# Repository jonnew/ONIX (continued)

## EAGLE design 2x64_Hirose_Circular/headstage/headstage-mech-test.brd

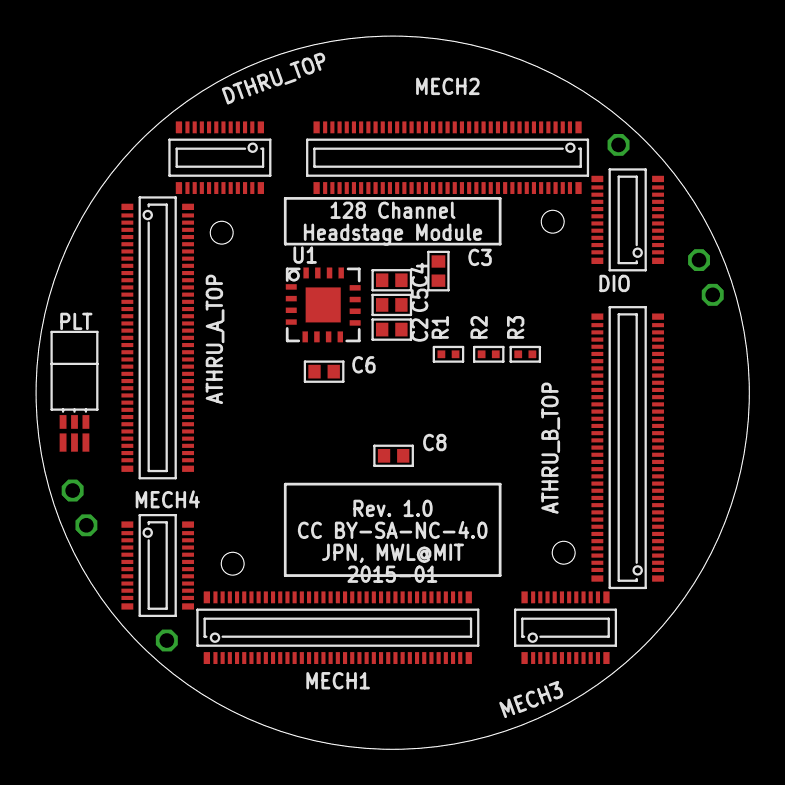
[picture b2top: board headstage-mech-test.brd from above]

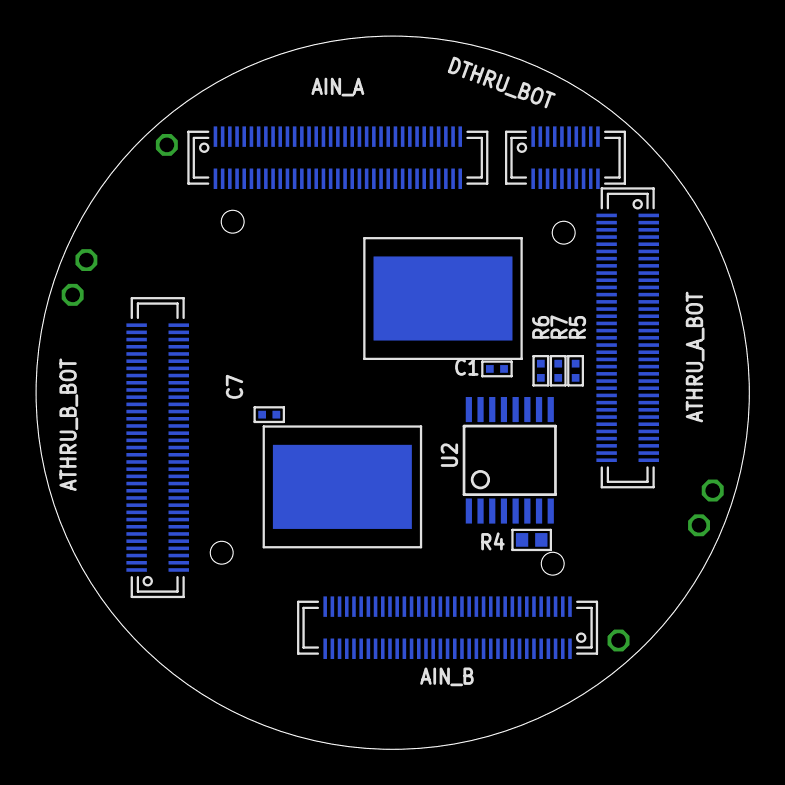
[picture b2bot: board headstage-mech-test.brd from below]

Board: 2 copper layers, 39.6 x 39.6 mm, 39 parts (14 on the bottom side), 168 nets, no tracks yet.

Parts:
AIN_A: DF40REC; DF40-70REC
AIN_B: DF40REC; DF40-70REC
ATHRU_A_BOT: DF40REC; DF40-70REC
ATHRU_A_TOP: DF40HEAD; DF40-70HEAD
ATHRU_B_BOT: DF40REC; DF40-70REC
ATHRU_B_TOP: DF40HEAD; DF40-70HEAD
C1, C7: 10n; 0201
C2, C3, C4, C5, C6, C8: .1uF; 0402
DIO: DF40HEAD; DF40-20HEAD
DTHRU_BOT: DF40REC; DF40-20REC
DTHRU_TOP: DF40HEAD; DF40-20HEAD
E$1, E$2: RHD2164_COB_MECH
GND, GND.: GND; TESTPOINT_SMALL
MECH1, MECH2: DF40HEAD; DF40-70HEAD
MECH3, MECH4: DF40HEAD; DF40-20HEAD
PLT: PZN-06; OMNETICS_PZN-06-AA
R1, R2, R3: 100; 0201
R4: 0; 0402
R5, R6, R7: 100k; 0201
REF1, REF2: REF; TESTPOINT_SMALL
U1: ADXL335
U2: 74HC4053; TSSOP-16
VCC1, VCC2: VCC; TESTPOINT_SMALL

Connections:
AGND_THRU_1: ATHRU_A_BOT.34, ATHRU_A_BOT.35, ATHRU_A_TOP.34, ATHRU_A_TOP.35
AGND_THRU_2: ATHRU_A_BOT.69, ATHRU_A_BOT.70, ATHRU_A_TOP.69, ATHRU_A_TOP.70
AGND_THRU_3: ATHRU_B_BOT.34, ATHRU_B_BOT.35, ATHRU_B_TOP.34, ATHRU_B_TOP.35
AGND_THRU_4: ATHRU_B_BOT.69, ATHRU_B_BOT.70, ATHRU_B_TOP.69, ATHRU_B_TOP.70
AUXOUT_A_THRU: DTHRU_BOT.4, DTHRU_TOP.4
AUXOUT_B_THRU: DTHRU_BOT.5, DTHRU_TOP.5
BATH: PLT.B1, U2.3
CS+: DIO.12, R1.2
CS+_THRU: DTHRU_BOT.12, DTHRU_TOP.12
CS-: DIO.11, R1.1
CS-_THRU: DTHRU_BOT.11, DTHRU_TOP.11
DGND_THRU: DTHRU_BOT.1, DTHRU_BOT.2, DTHRU_BOT.3, DTHRU_BOT.6, DTHRU_BOT.7, DTHRU_BOT.8, DTHRU_BOT.9, DTHRU_TOP.1, DTHRU_TOP.2, DTHRU_TOP.3, DTHRU_TOP.6, DTHRU_TOP.7, DTHRU_TOP.8, DTHRU_TOP.9
GND: AIN_A.34, AIN_A.35, AIN_A.69, AIN_A.70, AIN_B.34, AIN_B.35, AIN_B.69, AIN_B.70, C1.2, C2.2, C3.2, C4.1, C5.1, C6.1, C7.2, C8.2, DIO.1, DIO.2, DIO.3, DIO.5, DIO.6, DIO.7, GND.1, GND..1, PLT.B3, R4.1, R5.1, R6.1, R7.1, U1.COM1, U1.COM2, U1.COM3, U1.COM4, U1.ST, U2.6, U2.7, U2.8
MISO1+_THRU: DTHRU_BOT.18, DTHRU_TOP.18
MISO1-_THRU: DTHRU_BOT.17, DTHRU_TOP.17
MISO2+_THRU: DTHRU_BOT.20, DTHRU_TOP.20
MISO2-_THRU: DTHRU_BOT.19, DTHRU_TOP.19
MOSI+: DIO.16, R3.2
MOSI+_THRU: DTHRU_BOT.16, DTHRU_TOP.16
MOSI-: DIO.15, R3.1
MOSI-_THRU: DTHRU_BOT.15, DTHRU_TOP.15
unnamed: ATHRU_B_BOT.33, ATHRU_B_TOP.33
unnamed: ATHRU_B_BOT.32, ATHRU_B_TOP.32
unnamed: ATHRU_B_BOT.31, ATHRU_B_TOP.31
unnamed: ATHRU_B_BOT.30, ATHRU_B_TOP.30
unnamed: ATHRU_B_BOT.29, ATHRU_B_TOP.29
unnamed: ATHRU_B_BOT.28, ATHRU_B_TOP.28
unnamed: ATHRU_B_BOT.27, ATHRU_B_TOP.27
unnamed: ATHRU_B_BOT.26, ATHRU_B_TOP.26
unnamed: ATHRU_B_BOT.25, ATHRU_B_TOP.25
unnamed: ATHRU_B_BOT.24, ATHRU_B_TOP.24
unnamed: ATHRU_B_BOT.23, ATHRU_B_TOP.23
unnamed: ATHRU_B_BOT.22, ATHRU_B_TOP.22
unnamed: ATHRU_B_BOT.21, ATHRU_B_TOP.21
unnamed: ATHRU_B_BOT.20, ATHRU_B_TOP.20
unnamed: ATHRU_B_BOT.19, ATHRU_B_TOP.19
unnamed: ATHRU_B_BOT.18, ATHRU_B_TOP.18
unnamed: ATHRU_B_BOT.17, ATHRU_B_TOP.17
unnamed: ATHRU_B_BOT.16, ATHRU_B_TOP.16
unnamed: ATHRU_B_BOT.15, ATHRU_B_TOP.15
unnamed: ATHRU_B_BOT.14, ATHRU_B_TOP.14
unnamed: ATHRU_B_BOT.13, ATHRU_B_TOP.13
unnamed: ATHRU_B_BOT.12, ATHRU_B_TOP.12
unnamed: ATHRU_B_BOT.11, ATHRU_B_TOP.11
unnamed: PLT.T1, R7.2, U2.11
unnamed: PLT.T2, R6.2, U2.10
unnamed: PLT.T3, R5.2, U2.9
unnamed: R4.2, U2.5
unnamed: PLT.B2, U2.1, U2.13
unnamed: ATHRU_B_BOT.10, ATHRU_B_TOP.10
unnamed: ATHRU_B_BOT.9, ATHRU_B_TOP.9
unnamed: ATHRU_B_BOT.8, ATHRU_B_TOP.8
unnamed: ATHRU_B_BOT.7, ATHRU_B_TOP.7
unnamed: ATHRU_B_BOT.6, ATHRU_B_TOP.6
unnamed: ATHRU_B_BOT.5, ATHRU_B_TOP.5
unnamed: ATHRU_B_BOT.4, ATHRU_B_TOP.4
unnamed: ATHRU_B_BOT.3, ATHRU_B_TOP.3
unnamed: ATHRU_B_BOT.2, ATHRU_B_TOP.2
unnamed: ATHRU_B_BOT.38, ATHRU_B_TOP.38
unnamed: ATHRU_B_BOT.39, ATHRU_B_TOP.39
unnamed: ATHRU_B_BOT.40, ATHRU_B_TOP.40
unnamed: ATHRU_B_BOT.41, ATHRU_B_TOP.41
unnamed: ATHRU_B_BOT.42, ATHRU_B_TOP.42
unnamed: ATHRU_B_BOT.43, ATHRU_B_TOP.43
unnamed: ATHRU_B_BOT.44, ATHRU_B_TOP.44
unnamed: ATHRU_B_BOT.45, ATHRU_B_TOP.45
unnamed: ATHRU_B_BOT.46, ATHRU_B_TOP.46
unnamed: ATHRU_B_BOT.47, ATHRU_B_TOP.47
unnamed: ATHRU_B_BOT.48, ATHRU_B_TOP.48
unnamed: ATHRU_B_BOT.49, ATHRU_B_TOP.49
unnamed: ATHRU_B_BOT.50, ATHRU_B_TOP.50
unnamed: ATHRU_B_BOT.51, ATHRU_B_TOP.51
unnamed: ATHRU_B_BOT.52, ATHRU_B_TOP.52
unnamed: ATHRU_B_BOT.53, ATHRU_B_TOP.53
unnamed: ATHRU_B_BOT.54, ATHRU_B_TOP.54
unnamed: ATHRU_B_BOT.55, ATHRU_B_TOP.55
unnamed: ATHRU_B_BOT.56, ATHRU_B_TOP.56
unnamed: ATHRU_B_BOT.57, ATHRU_B_TOP.57
unnamed: ATHRU_B_BOT.58, ATHRU_B_TOP.58
unnamed: ATHRU_B_BOT.59, ATHRU_B_TOP.59
unnamed: ATHRU_B_BOT.60, ATHRU_B_TOP.60
unnamed: ATHRU_B_BOT.61, ATHRU_B_TOP.61
unnamed: ATHRU_B_BOT.62, ATHRU_B_TOP.62
unnamed: ATHRU_B_BOT.63, ATHRU_B_TOP.63
unnamed: ATHRU_B_BOT.64, ATHRU_B_TOP.64
unnamed: ATHRU_B_BOT.65, ATHRU_B_TOP.65
unnamed: ATHRU_B_BOT.66, ATHRU_B_TOP.66
unnamed: ATHRU_B_BOT.67, ATHRU_B_TOP.67
unnamed: ATHRU_B_BOT.68, ATHRU_B_TOP.68
unnamed: ATHRU_A_BOT.33, ATHRU_A_TOP.33
unnamed: ATHRU_A_BOT.32, ATHRU_A_TOP.32
unnamed: ATHRU_A_BOT.31, ATHRU_A_TOP.31
unnamed: ATHRU_A_BOT.30, ATHRU_A_TOP.30
unnamed: ATHRU_A_BOT.29, ATHRU_A_TOP.29
unnamed: ATHRU_A_BOT.28, ATHRU_A_TOP.28
unnamed: ATHRU_A_BOT.27, ATHRU_A_TOP.27
unnamed: ATHRU_A_BOT.26, ATHRU_A_TOP.26
unnamed: ATHRU_A_BOT.25, ATHRU_A_TOP.25
unnamed: ATHRU_A_BOT.24, ATHRU_A_TOP.24
unnamed: ATHRU_A_BOT.23, ATHRU_A_TOP.23
unnamed: ATHRU_A_BOT.22, ATHRU_A_TOP.22
unnamed: ATHRU_A_BOT.21, ATHRU_A_TOP.21
unnamed: ATHRU_A_BOT.20, ATHRU_A_TOP.20
unnamed: ATHRU_A_BOT.19, ATHRU_A_TOP.19
unnamed: ATHRU_A_BOT.18, ATHRU_A_TOP.18
unnamed: ATHRU_A_BOT.17, ATHRU_A_TOP.17
unnamed: ATHRU_A_BOT.16, ATHRU_A_TOP.16
unnamed: ATHRU_A_BOT.15, ATHRU_A_TOP.15
unnamed: ATHRU_A_BOT.14, ATHRU_A_TOP.14
unnamed: ATHRU_A_BOT.13, ATHRU_A_TOP.13
unnamed: ATHRU_A_BOT.12, ATHRU_A_TOP.12
unnamed: ATHRU_A_BOT.11, ATHRU_A_TOP.11
unnamed: ATHRU_A_BOT.10, ATHRU_A_TOP.10
unnamed: ATHRU_A_BOT.9, ATHRU_A_TOP.9
unnamed: ATHRU_A_BOT.8, ATHRU_A_TOP.8
unnamed: ATHRU_A_BOT.7, ATHRU_A_TOP.7
unnamed: ATHRU_A_BOT.6, ATHRU_A_TOP.6
unnamed: ATHRU_A_BOT.5, ATHRU_A_TOP.5
unnamed: ATHRU_A_BOT.4, ATHRU_A_TOP.4
unnamed: ATHRU_A_BOT.3, ATHRU_A_TOP.3
unnamed: ATHRU_A_BOT.2, ATHRU_A_TOP.2
unnamed: ATHRU_A_BOT.38, ATHRU_A_TOP.38
unnamed: ATHRU_A_BOT.39, ATHRU_A_TOP.39
unnamed: ATHRU_A_BOT.40, ATHRU_A_TOP.40
unnamed: ATHRU_A_BOT.41, ATHRU_A_TOP.41
unnamed: ATHRU_A_BOT.42, ATHRU_A_TOP.42
unnamed: ATHRU_A_BOT.43, ATHRU_A_TOP.43
unnamed: ATHRU_A_BOT.44, ATHRU_A_TOP.44
unnamed: ATHRU_A_BOT.45, ATHRU_A_TOP.45
unnamed: ATHRU_A_BOT.46, ATHRU_A_TOP.46
unnamed: ATHRU_A_BOT.47, ATHRU_A_TOP.47
unnamed: ATHRU_A_BOT.48, ATHRU_A_TOP.48
unnamed: ATHRU_A_BOT.49, ATHRU_A_TOP.49
unnamed: ATHRU_A_BOT.50, ATHRU_A_TOP.50
unnamed: ATHRU_A_BOT.51, ATHRU_A_TOP.51
unnamed: ATHRU_A_BOT.52, ATHRU_A_TOP.52
unnamed: ATHRU_A_BOT.53, ATHRU_A_TOP.53
unnamed: ATHRU_A_BOT.54, ATHRU_A_TOP.54
unnamed: ATHRU_A_BOT.55, ATHRU_A_TOP.55
unnamed: ATHRU_A_BOT.56, ATHRU_A_TOP.56
unnamed: ATHRU_A_BOT.57, ATHRU_A_TOP.57
unnamed: ATHRU_A_BOT.58, ATHRU_A_TOP.58
unnamed: ATHRU_A_BOT.59, ATHRU_A_TOP.59
unnamed: ATHRU_A_BOT.60, ATHRU_A_TOP.60
unnamed: ATHRU_A_BOT.61, ATHRU_A_TOP.61
unnamed: ATHRU_A_BOT.62, ATHRU_A_TOP.62
unnamed: ATHRU_A_BOT.63, ATHRU_A_TOP.63
unnamed: ATHRU_A_BOT.64, ATHRU_A_TOP.64
unnamed: ATHRU_A_BOT.65, ATHRU_A_TOP.65
unnamed: ATHRU_A_BOT.66, ATHRU_A_TOP.66
unnamed: ATHRU_A_BOT.67, ATHRU_A_TOP.67
unnamed: ATHRU_A_BOT.68, ATHRU_A_TOP.68
unnamed: ATHRU_B_BOT.37, ATHRU_B_TOP.37
unnamed: ATHRU_A_BOT.37, ATHRU_A_TOP.37
REF: AIN_A.1, AIN_A.36, AIN_B.1, AIN_B.36, REF1.1, REF2.1, U2.4
REF_THRU_1: ATHRU_A_BOT.36, ATHRU_A_TOP.36
REF_THRU_2: ATHRU_A_BOT.1, ATHRU_A_TOP.1
REF_THRU_3: ATHRU_B_BOT.36, ATHRU_B_TOP.36
REF_THRU_4: ATHRU_B_BOT.1, ATHRU_B_TOP.1
SCLK+: DIO.14, R2.2
SCLK+_THRU: DTHRU_BOT.14, DTHRU_TOP.14
SCLK-: DIO.13, R2.1
SCLK-_THRU: DTHRU_BOT.13, DTHRU_TOP.13
VCC: C2.1, C3.1, C8.1, DIO.8, DIO.9, DIO.10, U1.VS1, U1.VS2, U2.16, VCC1.1, VCC2.1
VDD_THRU: DTHRU_BOT.10, DTHRU_TOP.10
XOUT1: C4.2, U1.XOUT
YOUT1: C5.2, U1.YOUT
ZOUT1: C6.2, U1.ZOUT

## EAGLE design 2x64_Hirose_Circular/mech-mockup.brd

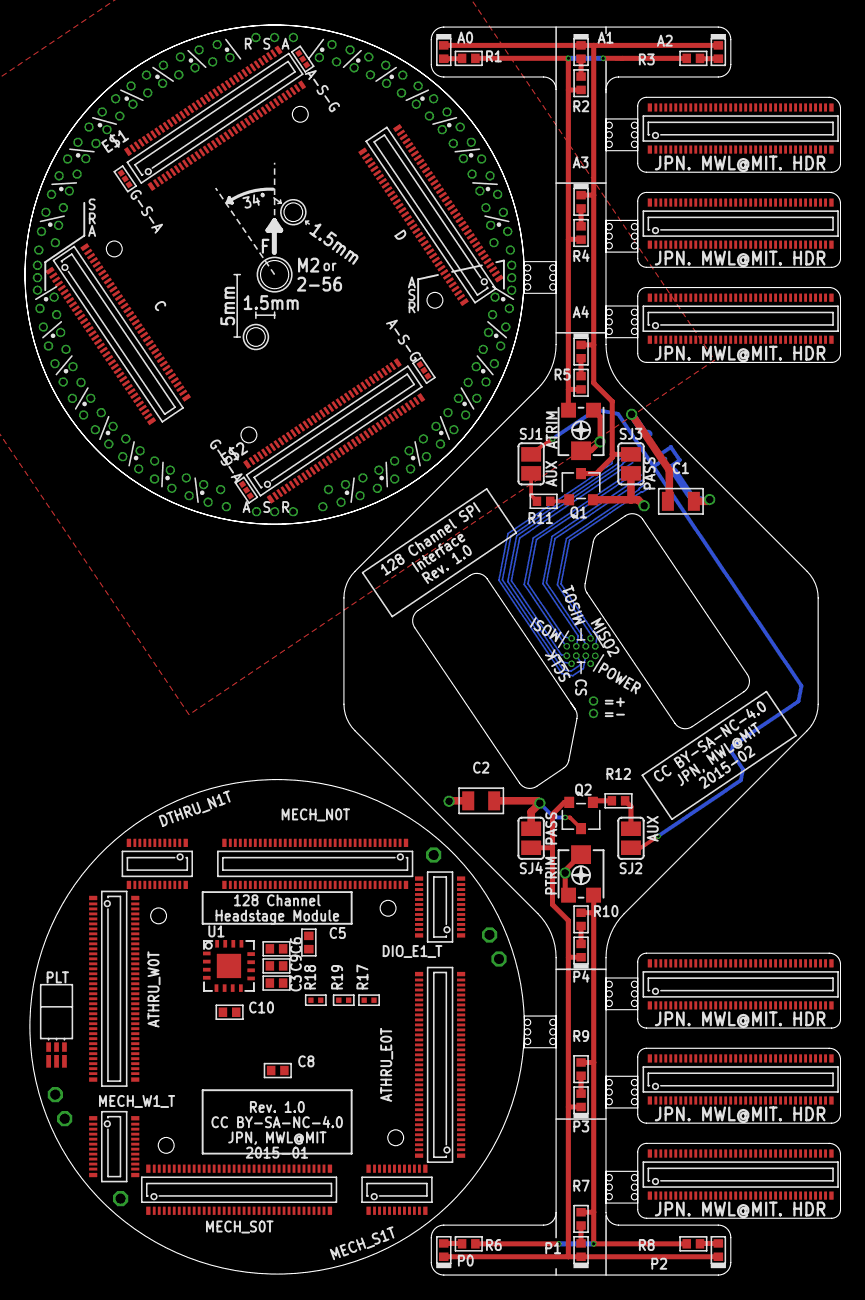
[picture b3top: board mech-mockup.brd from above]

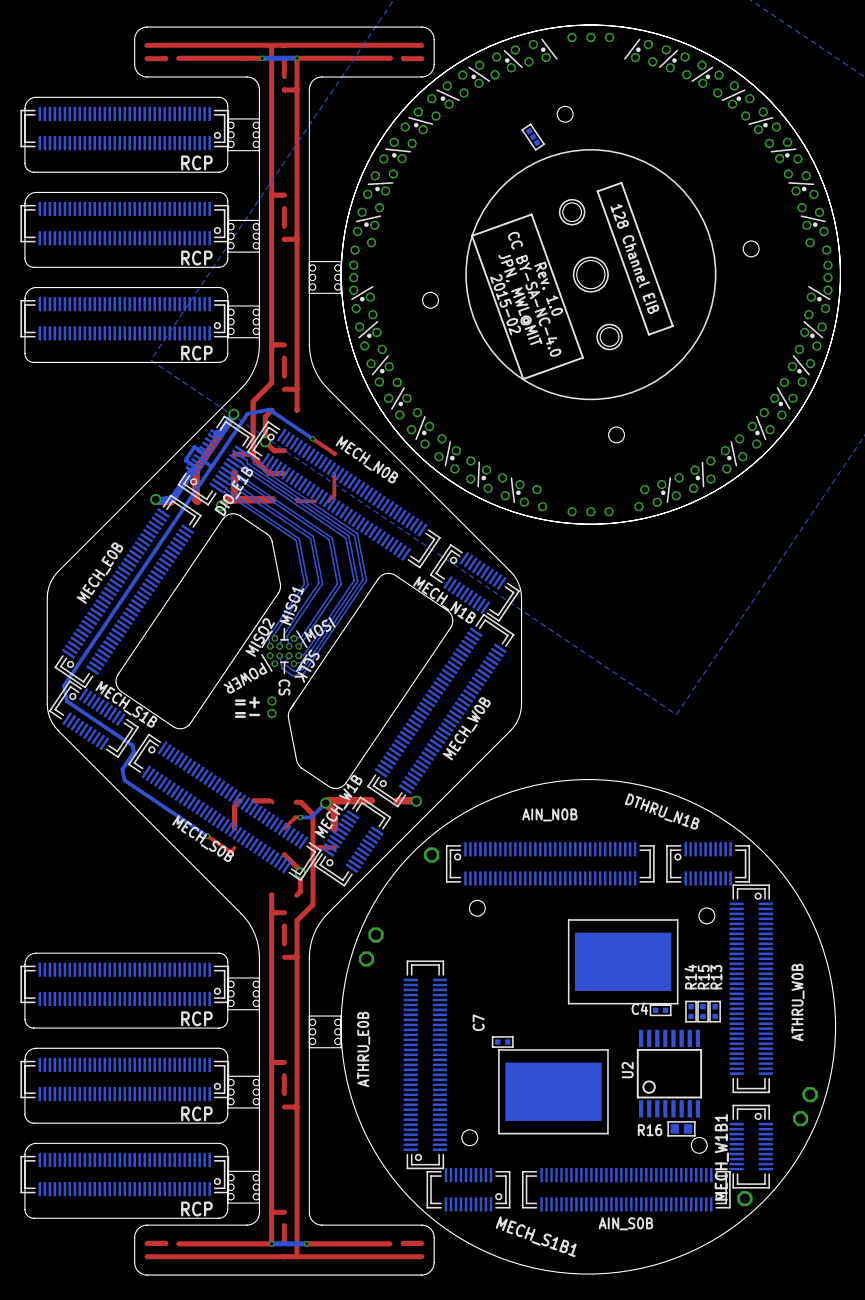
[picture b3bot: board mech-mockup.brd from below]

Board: 4 copper layers, 65.3 x 100.2 mm, 159 parts (48 on the bottom side), 32 nets.

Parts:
A0, A1, A2, A3, A4: RED; LED-0402
AGND_A0, AGND_A1: LRG_GP; GOLDPIN_0.5ID_0.7OD
AGND_B0, AGND_B1: LRG_GP; GOLDPIN_0.5ID_0.7OD
AIN_N0B: DF40REC; DF40-70REC
AIN_S0B: DF40REC; DF40-70REC
ATHRU_A_BOT, ATHRU_A_BOT1, ATHRU_A_BOT2, ATHRU_A_BOT3, ATHRU_A_BOT4, ATHRU_A_BOT5: DF40REC; DF40-70REC
ATHRU_A_TOP, ATHRU_A_TOP1, ATHRU_A_TOP2, ATHRU_A_TOP3, ATHRU_A_TOP4, ATHRU_A_TOP5: DF40HEAD; DF40-70HEAD
ATHRU_E0B: DF40REC; DF40-70REC
ATHRU_E0T: DF40HEAD; DF40-70HEAD
ATHRU_W0B: DF40REC; DF40-70REC
ATHRU_W0T: DF40HEAD; DF40-70HEAD
ATRIM: 2k; EIA/EIAJ
C: DF40HEAD; DF40-70HEAD
C1, C2: 10uF; 0805
C3, C5, C6, C8, C9, C10: .1uF; 0402
C4, C7: 10n; 0201
CS+: TP_SPI_WIRE+; SPI_WIRE+
CS-: TP_SPI_WIRE-; SPI_WIRE-
D: DF40HEAD; DF40-70HEAD
DIO_E1B: DF40-20REC
DIO_E1_T: DF40HEAD; DF40-20HEAD
DTHRU_N1B: DF40REC; DF40-20REC
DTHRU_N1T: DF40HEAD; DF40-20HEAD
E$1, E$2: DF40-70HEAD
E$3, E$4: RHD2164_COB_MECH
GND: TP_SPI_WIRE-; SPI_WIRE-
GND1, GND.: GND; TESTPOINT_SMALL
MECH_E0B: DF40-70REC
MECH_N0B: DF40-70REC
MECH_N0T: DF40HEAD; DF40-70HEAD
MECH_N1B: DF40-20REC
MECH_S0B: DF40-70REC
MECH_S0T: DF40HEAD; DF40-70HEAD
MECH_S1B: DF40-20REC
MECH_S1B1: DF40REC; DF40-20REC
MECH_S1T: DF40HEAD; DF40-20HEAD
MECH_W0B: DF40-70REC
MECH_W1B: DF40-20REC
MECH_W1B1: DF40REC; DF40-20REC
MECH_W1_T: DF40HEAD; DF40-20HEAD
MIS02+: TP_SPI_WIRE+; SPI_WIRE+
MISO1+: TP_SPI_WIRE+; SPI_WIRE+
MISO1-, MISO2-: TP_SPI_WIRE-; SPI_WIRE-
MOSI+: TP_SPI_WIRE+; SPI_WIRE+
MOSI-: TP_SPI_WIRE-; SPI_WIRE-
P0, P1, P2, P3, P4: BLUE; LED-0402
PLT: PZN-06; OMNETICS_PZN-06-AA
PTRIM: 2k; EIA/EIAJ
Q1: SSM3K324; SOT23-GSD
Q2: SSM3J328; SOT23-GSD
R1, R2, R3, R4, R5, R6, R7, R8, R9, R10: 82; 0402
R11, R12: 470; 0402
R13, R14, R15: 100k; 0201
R16: 0; 0402
R17, R18, R19: 100; 0201
REF1, REF2: REF; TESTPOINT_SMALL
REF_A0, REF_A1: LRG_GP; GOLDPIN_0.5ID_0.7OD
REF_B0, REF_B1: LRG_GP; GOLDPIN_0.5ID_0.7OD
SCLK+: TP_SPI_WIRE+; SPI_WIRE+
SCLK-: TP_SPI_WIRE-; SPI_WIRE-
SHLD_A0, SHLD_A1: LRG_GP; GOLDPIN_0.5ID_0.7OD
SHLD_B0, SHLD_B1: LRG_GP; GOLDPIN_0.5ID_0.7OD
SJ1, SJ2: AUX; SJ
SJ3, SJ4: PASS; SJ
SJ_A0, SJ_A1, SJ_A2: SJ_2_0201
SJ_B0, SJ_B1: SJ_2_0201
TET0: 0; TETRODE_128_0.5ID_0.7OD
TET1: 1; TETRODE_128_0.5ID_0.7OD
TET2: 2; TETRODE_128_0.5ID_0.7OD
TET3: 3; TETRODE_128_0.5ID_0.7OD
TET4: 4; TETRODE_128_0.5ID_0.7OD
TET5: 5; TETRODE_128_0.5ID_0.7OD
TET6: 6; TETRODE_128_0.5ID_0.7OD
TET7: 7; TETRODE_128_0.5ID_0.7OD
TET8: 8; TETRODE_128_0.5ID_0.7OD
TET9: 9; TETRODE_128_0.5ID_0.7OD
TET10: 10; TETRODE_128_0.5ID_0.7OD
TET11: 11; TETRODE_128_0.5ID_0.7OD
TET12: 12; TETRODE_128_0.5ID_0.7OD
TET13: 13; TETRODE_128_0.5ID_0.7OD
TET14: 14; TETRODE_128_0.5ID_0.7OD
TET15: 15; TETRODE_128_0.5ID_0.7OD
TET16: 16; TETRODE_128_0.5ID_0.7OD
TET17: 17; TETRODE_128_0.5ID_0.7OD
TET18: 18; TETRODE_128_0.5ID_0.7OD
TET19: 19; TETRODE_128_0.5ID_0.7OD
TET20: 20; TETRODE_128_0.5ID_0.7OD
TET21: 21; TETRODE_128_0.5ID_0.7OD
TET22: 22; TETRODE_128_0.5ID_0.7OD
TET23: 23; TETRODE_128_0.5ID_0.7OD
TET24: 24; TETRODE_128_0.5ID_0.7OD
TET25: 25; TETRODE_128_0.5ID_0.7OD
TET26: 26; TETRODE_128_0.5ID_0.7OD
TET27: 27; TETRODE_128_0.5ID_0.7OD
TET28: 28; TETRODE_128_0.5ID_0.7OD
TET29: 29; TETRODE_128_0.5ID_0.7OD
TET30: 30; TETRODE_128_0.5ID_0.7OD
TET31: 31; TETRODE_128_0.5ID_0.7OD
U1: ADXL335
U2: 74HC4053; TSSOP-16
U$1: EIB_MOUNT_A
VCC: TP_SPI_WIRE+; SPI_WIRE+
VCC1, VCC2: VCC; TESTPOINT_SMALL

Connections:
AUXOUTB: DIO_E1B.4, SJ1.1, SJ2.1
B2: P0.C, P1.C, P2.C, P3.C, P4.C, Q2.S, SJ4.1
CS+: CS+.P$1, DIO_E1B.12
CS-: CS-.P$1, DIO_E1B.11
F1: A0.C, A1.C, A2.C, A3.C, A4.C, Q1.D, SJ3.1
GND: C1.2, C2.2, DIO_E1B.1, DIO_E1B.2, DIO_E1B.3, DIO_E1B.5, DIO_E1B.6, DIO_E1B.7, GND.P$1, Q1.S, Q2.D, SJ3.2, SJ4.2
GND1: SJ_A0.1, SJ_A1.1, SJ_A2.1, SJ_A2.2, SJ_B0.1, SJ_B1.1
MIS02-: DIO_E1B.19, MISO2-.P$1
MISO1+: DIO_E1B.18, MISO1+.P$1
MISO1-: DIO_E1B.17, MISO1-.P$1
MISO2+: DIO_E1B.20, MIS02+.P$1
MOSI+: DIO_E1B.16, MOSI+.P$1
MOSI-: DIO_E1B.15, MOSI-.P$1
unnamed: ATRIM.E, R1.2, R2.2, R3.2, R4.2, R5.2
unnamed: P0.A, R6.1
unnamed: A0.A, R1.1
unnamed: R12.2, SJ2.2
unnamed: Q2.G, R12.1
unnamed: PTRIM.E, R6.2, R7.2, R8.2, R9.2, R10.2
unnamed: A1.A, R2.1
unnamed: A2.A, R3.1
unnamed: A3.A, R4.1
unnamed: P3.A, R9.1
unnamed: P1.A, R7.1
unnamed: P2.A, R8.1
unnamed: A4.A, R5.1
unnamed: P4.A, R10.1
unnamed: Q1.G, R11.1
unnamed: R11.2, SJ1.2
SCLK+: DIO_E1B.14, SCLK+.P$1
SCLK-: DIO_E1B.13, SCLK-.P$1
VCC: ATRIM.A, ATRIM.S, C1.1, C2.1, DIO_E1B.8, DIO_E1B.9, DIO_E1B.10, PTRIM.A, PTRIM.S, VCC.P$1

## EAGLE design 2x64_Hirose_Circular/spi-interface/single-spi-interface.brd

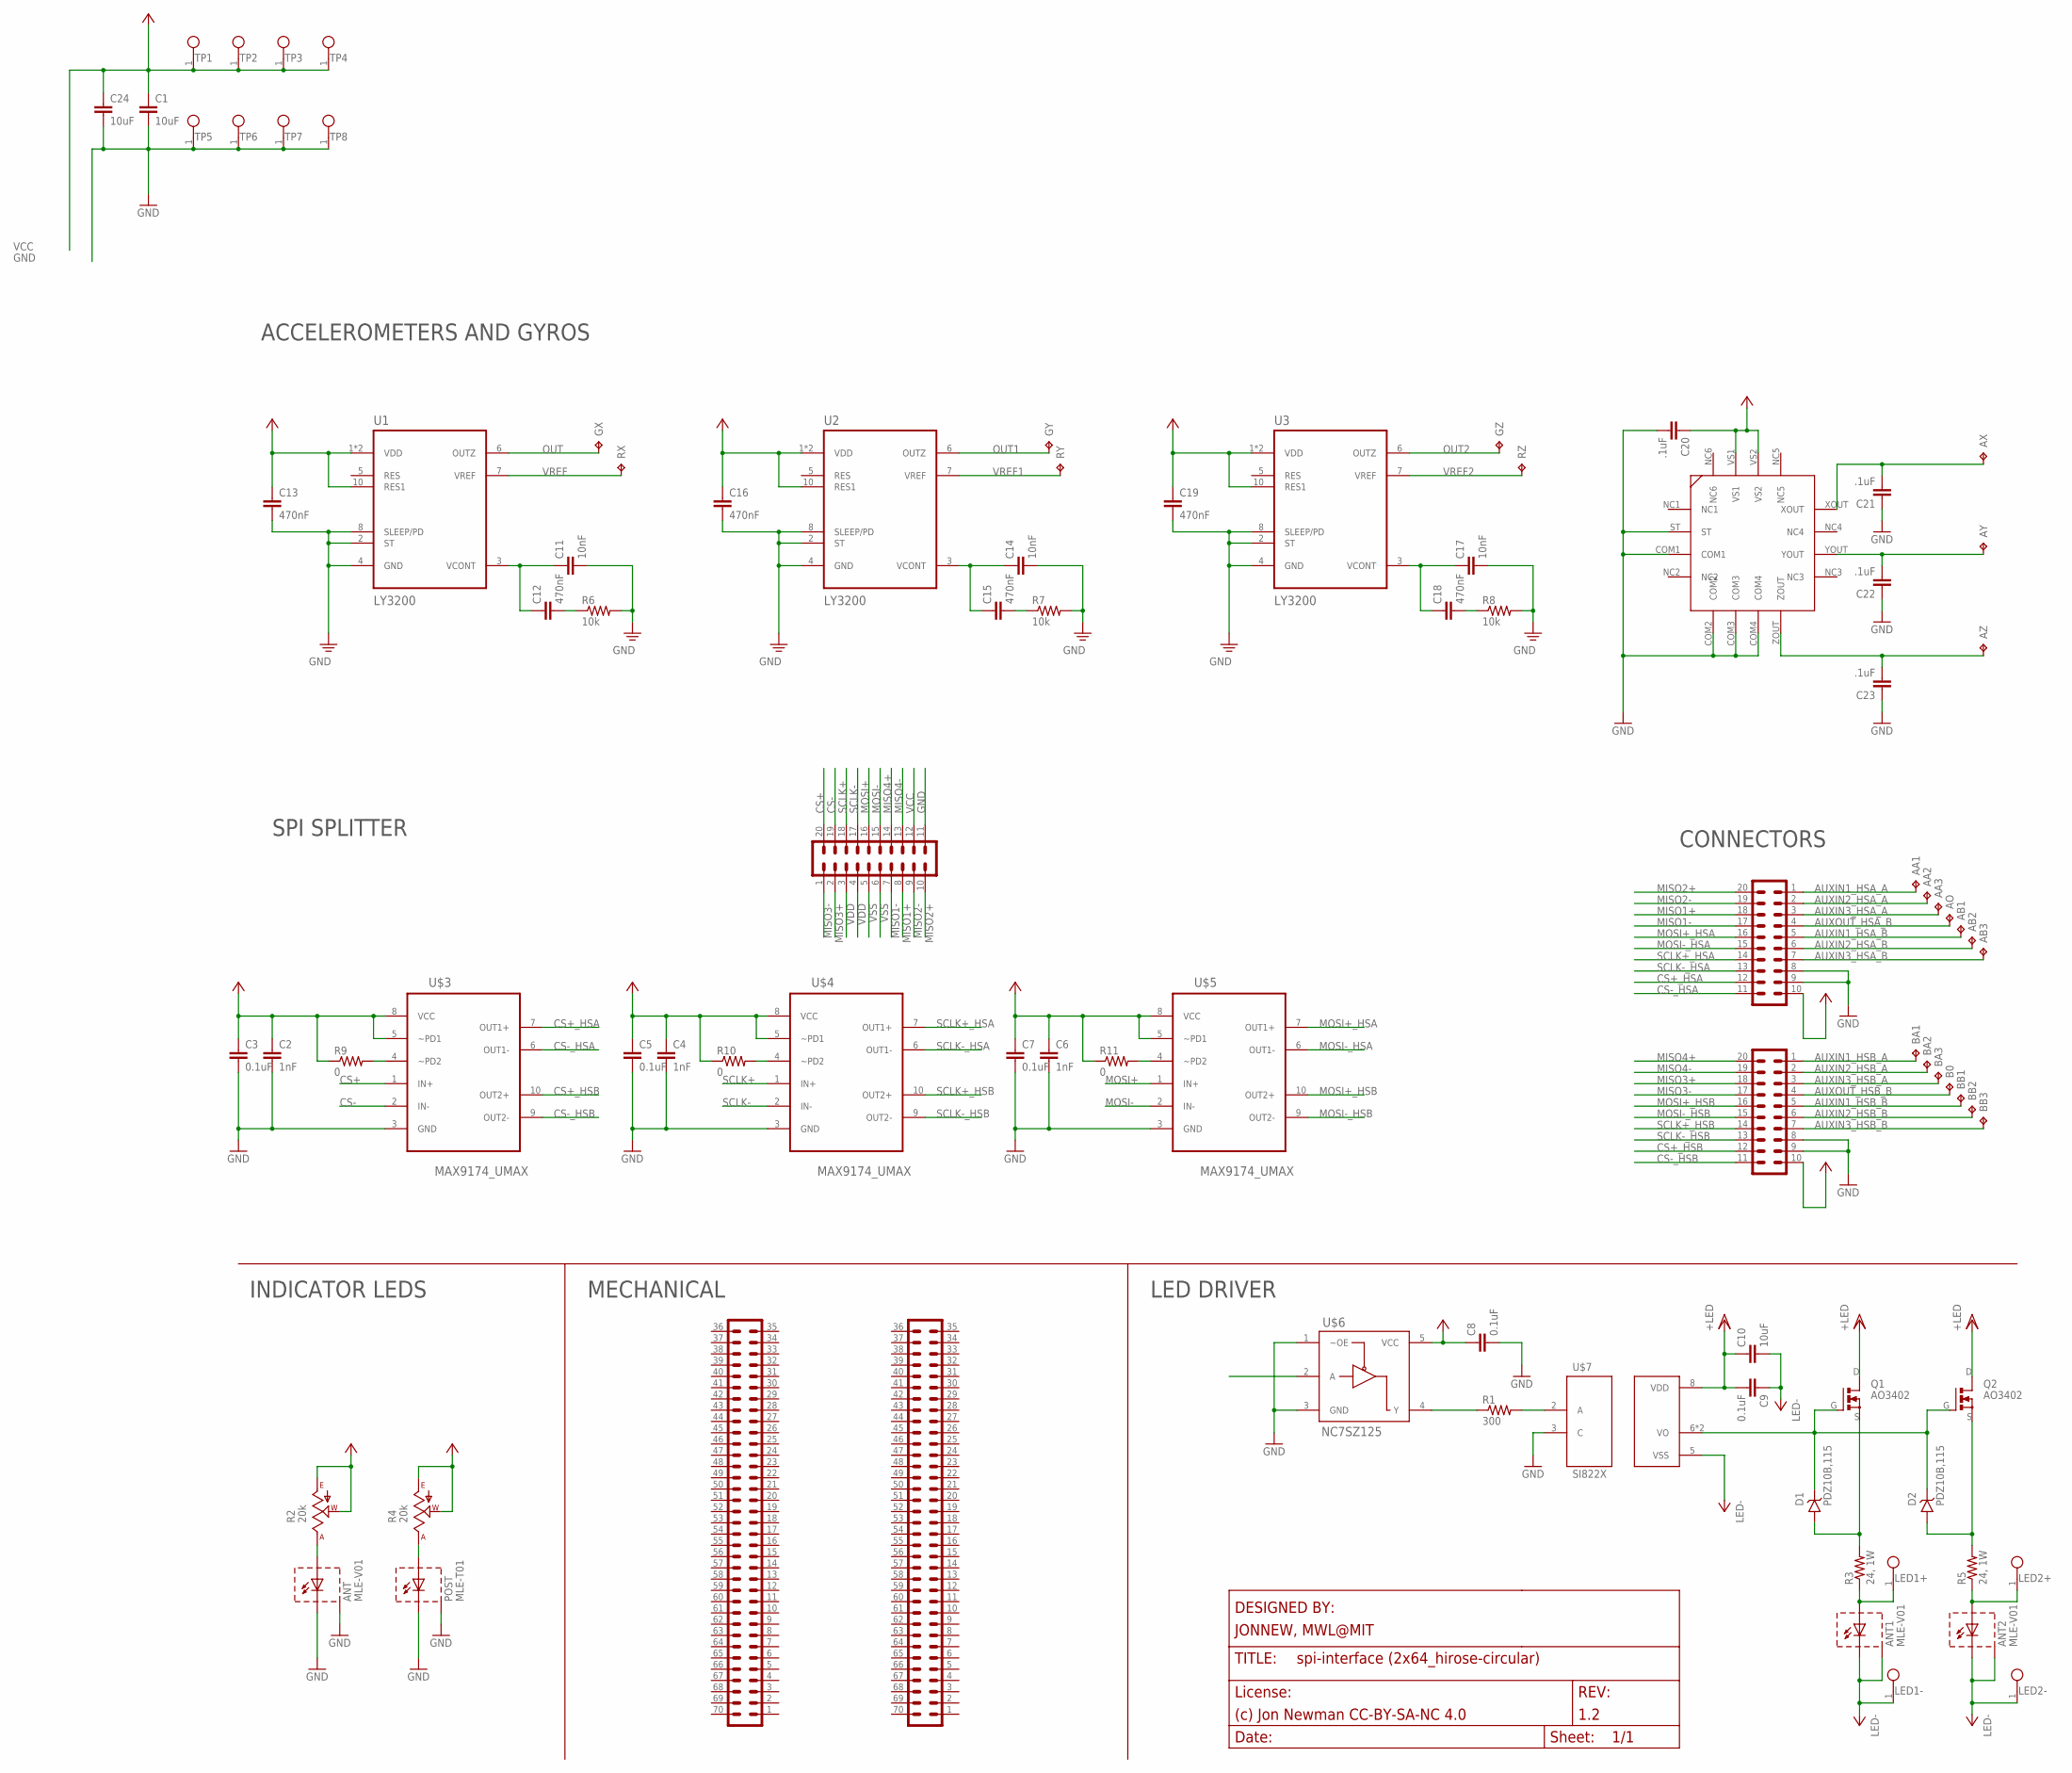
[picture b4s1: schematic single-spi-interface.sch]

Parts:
AA1, AA2, AA3: TP_0.035IN; TESTPOINT_0.035IN
AB1, AB2, AB3: TP_0.035IN; TESTPOINT_0.035IN
ANT, ANT1, ANT2: MLE-V01; LED-MLE
AO: TP_0.035IN; TESTPOINT_0.035IN
AX: TP_0.035IN; TESTPOINT_0.035IN
AY: TP_0.035IN; TESTPOINT_0.035IN
AZ: TP_0.035IN; TESTPOINT_0.035IN
B0: TP_0.035IN; TESTPOINT_0.035IN
BA1, BA2, BA3: TP_0.035IN; TESTPOINT_0.035IN
BB1, BB2, BB3: TP_0.035IN; TESTPOINT_0.035IN
C1, C10, C24: 10uF; 0805
C2, C4, C6: 1nF; 0402
C3, C5, C7, C8, C9: 0.1uF; 0402
C11, C14, C17: 10nF; 0201
C12, C13, C15, C16, C18, C19: 470nF; 0201
C20: .1uF; 0402
C21, C22, C23: .1uF; 0201
D1, D2: PDZ10B,115; SOD-323
DIO_E1B, DIO_E1B1: PINHD-2X10_DF40-20REC; DF40-20REC
GX: TP_0.035IN; TESTPOINT_0.035IN
GY: TP_0.035IN; TESTPOINT_0.035IN
GZ: TP_0.035IN; TESTPOINT_0.035IN
LED1+, LED1-, LED2+, LED2-: TESTPOINT_SMALL
MECH_E0B: PINHD-2X35_DF40REC; DF40-70REC
MECH_W0B: PINHD-2X35_DF40REC; DF40-70REC
POST: MLE-T01; LED-MLE
Q1, Q2: AO3402; SOT23-GSD
R1: 300; 0402
R2, R4: 20k; SM-42/43W
R3, R5: 24, 1W; 0805
R6, R7, R8: 10k; 0201
R9, R10, R11: 0; 0201
RX: TP_0.035IN; TESTPOINT_0.035IN
RY: TP_0.035IN; TESTPOINT_0.035IN
RZ: TP_0.035IN; TESTPOINT_0.035IN
TP1, TP2, TP3, TP4, TP5, TP6, TP7, TP8: TESTPOINT_SMALL
U1, U2, U3: LY3200; LGA-10-COMPACT
U4: ADXL335
U$2: PINHD-2X10_T1M; T1M-10-T-DV
U$3, U$4, U$5: MAX9174_UMAX; 10-UMAX
U$6: NC7SZ125; SOT-23-5
U$7: SI822X; SOIC127P500X400-8N

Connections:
AUXIN1_HSA_A: AA1.1, DIO_E1B.1
AUXIN1_HSA_B: AB1.1, DIO_E1B.5
AUXIN1_HSB_A: BA1.1, DIO_E1B1.1
AUXIN1_HSB_B: BB1.1, DIO_E1B1.5
AUXIN2_HSA_A: AA2.1, DIO_E1B.2
AUXIN2_HSA_B: AB2.1, DIO_E1B.6
AUXIN2_HSB_A: BA2.1, DIO_E1B1.2
AUXIN2_HSB_B: BB2.1, DIO_E1B1.6
AUXIN3_HSA_A: AA3.1, DIO_E1B.3
AUXIN3_HSA_B: AB3.1, DIO_E1B.7
AUXIN3_HSB_A: BA3.1, DIO_E1B1.3
AUXIN3_HSB_B: BB3.1, DIO_E1B1.7
AUXOUT_HSA_B: AO.1, DIO_E1B.4
AUXOUT_HSB_B: B0.1, DIO_E1B1.4
CS+: U$2.20, U$3.1 (IN+)
CS+_HSA: DIO_E1B.12, U$3.7 (OUT1+)
CS+_HSB: DIO_E1B1.12, U$3.10 (OUT2+)
CS-: U$2.19, U$3.2 (IN-)
CS-_HSA: DIO_E1B.11, U$3.6 (OUT1-)
CS-_HSB: DIO_E1B1.11, U$3.9 (OUT2-)
GND: ANT.C1 (C), ANT.C2 (C), ANT.HS (BODY), C1.2, C2.2, C3.2, C4.2, C5.2, C6.2, C7.2, C8.2, C11.2, C13.2, C14.2, C16.2, C17.2, C19.2, C20.2, C21.1, C22.1, C23.1, C24.2, DIO_E1B.8, DIO_E1B.9, DIO_E1B1.8, DIO_E1B1.9, POST.C1 (C), POST.C2 (C), POST.HS (BODY), R6.2, R7.2, R8.2, TP5.1, TP6.1, TP7.1, TP8.1, U1.2 (ST), U1.4 (GND), U1.8 (SLEEP/PD), U2.2 (ST), U2.4 (GND), U2.8 (SLEEP/PD), U3.2 (ST), U3.4 (GND), U3.8 (SLEEP/PD), U4.COM1, U4.COM2, U4.COM3, U4.COM4, U4.ST, U$2.11, U$3.3 (GND), U$4.3 (GND), U$5.3 (GND), U$6.1 (~OE), U$6.3 (GND), U$7.3 (C)
MISO1+: DIO_E1B.18, U$2.8
MISO1-: DIO_E1B.17, U$2.7
MISO2+: DIO_E1B.20, U$2.10
MISO2-: DIO_E1B.19, U$2.9
MISO3+: DIO_E1B1.18, U$2.2
MISO3-: DIO_E1B1.17, U$2.1
MISO4+: DIO_E1B1.20, U$2.14
MISO4-: DIO_E1B1.19, U$2.13
MOSI+: U$2.16, U$5.1 (IN+)
MOSI+_HSA: DIO_E1B.16, U$5.7 (OUT1+)
MOSI+_HSB: DIO_E1B1.16, U$5.10 (OUT2+)
MOSI-: U$2.15, U$5.2 (IN-)
MOSI-_HSA: DIO_E1B.15, U$5.6 (OUT1-)
MOSI-_HSB: DIO_E1B1.15, U$5.9 (OUT2-)
unnamed: R1.2, U$7.2 (A)
unnamed: C11.1, C12.1, U1.3 (VCONT)
unnamed: ANT1.A1 (A), ANT1.A2 (A), LED1+.1, R3.1
unnamed: D1.A, Q1.S, R3.2
unnamed: R1.1, U$6.4 (Y)
unnamed: D1.C, D2.C, Q1.G, Q2.G, U$7.6 (VO), U$7.7 (VO)
unnamed: C12.2, R6.1
unnamed: ANT.A1 (A), ANT.A2 (A), R2.1 (A)
unnamed: C14.1, C15.1, U2.3 (VCONT)
unnamed: D2.A, Q2.S, R5.2
unnamed: ANT2.A1 (A), ANT2.A2 (A), LED2+.1, R5.1
unnamed: POST.A1 (A), POST.A2 (A), R4.1 (A)
unnamed: C15.2, R7.1
unnamed: C17.1, C18.1, U3.3 (VCONT)
unnamed: C18.2, R8.1
unnamed: R9.2, U$3.4 (~PD2)
unnamed: R11.2, U$5.4 (~PD2)
unnamed: R10.2, U$4.4 (~PD2)
OUT: GX.1, U1.6 (OUTZ)
OUT1: GY.1, U2.6 (OUTZ)
OUT2: GZ.1, U3.6 (OUTZ)
SCLK+: U$2.18, U$4.1 (IN+)
SCLK+_HSA: DIO_E1B.14, U$4.7 (OUT1+)
SCLK+_HSB: DIO_E1B1.14, U$4.10 (OUT2+)
SCLK-: U$2.17, U$4.2 (IN-)
SCLK-_HSA: DIO_E1B.13, U$4.6 (OUT1-)
SCLK-_HSB: DIO_E1B1.13, U$4.9 (OUT2-)
VCC: C1.1, C2.1, C3.1, C4.1, C5.1, C6.1, C7.1, C8.1, C13.1, C16.1, C19.1, C20.1, C24.1, DIO_E1B.10, DIO_E1B1.10, R2.2 (W), R2.3 (E), R4.2 (W), R4.3 (E), R9.1, R10.1, R11.1, TP1.1, TP2.1, TP3.1, TP4.1, U1.1 (VDD), U1.9 (VDD), U1.10 (RES1), U2.1 (VDD), U2.9 (VDD), U2.10 (RES1), U3.1 (VDD), U3.9 (VDD), U3.10 (RES1), U4.VS1, U4.VS2, U$2.12, U$3.5 (~PD1), U$3.8 (VCC), U$4.5 (~PD1), U$4.8 (VCC), U$5.5 (~PD1), U$5.8 (VCC), U$6.5 (VCC)
VDD: C9.2, C10.1, Q1.D, Q2.D, U$2.3, U$2.4, U$7.8 (VDD)
VREF: RX.1, U1.7 (VREF)
VREF1: RY.1, U2.7 (VREF)
VREF2: RZ.1, U3.7 (VREF)
VSS: ANT1.C1 (C), ANT1.C2 (C), ANT1.HS (BODY), ANT2.C1 (C), ANT2.C2 (C), ANT2.HS (BODY), C9.1, C10.2, LED1-.1, LED2-.1, U$2.5, U$2.6, U$7.5 (VSS)
XOUT1: AX.1, C21.2, U4.XOUT
YOUT1: AY.1, C22.2, U4.YOUT
ZOUT1: AZ.1, C23.2, U4.ZOUT

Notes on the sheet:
SPI SPLITTER
MECHANICAL
LED DRIVER
CONNECTORS
INDICATOR LEDS
ACCELEROMETERS AND GYROS

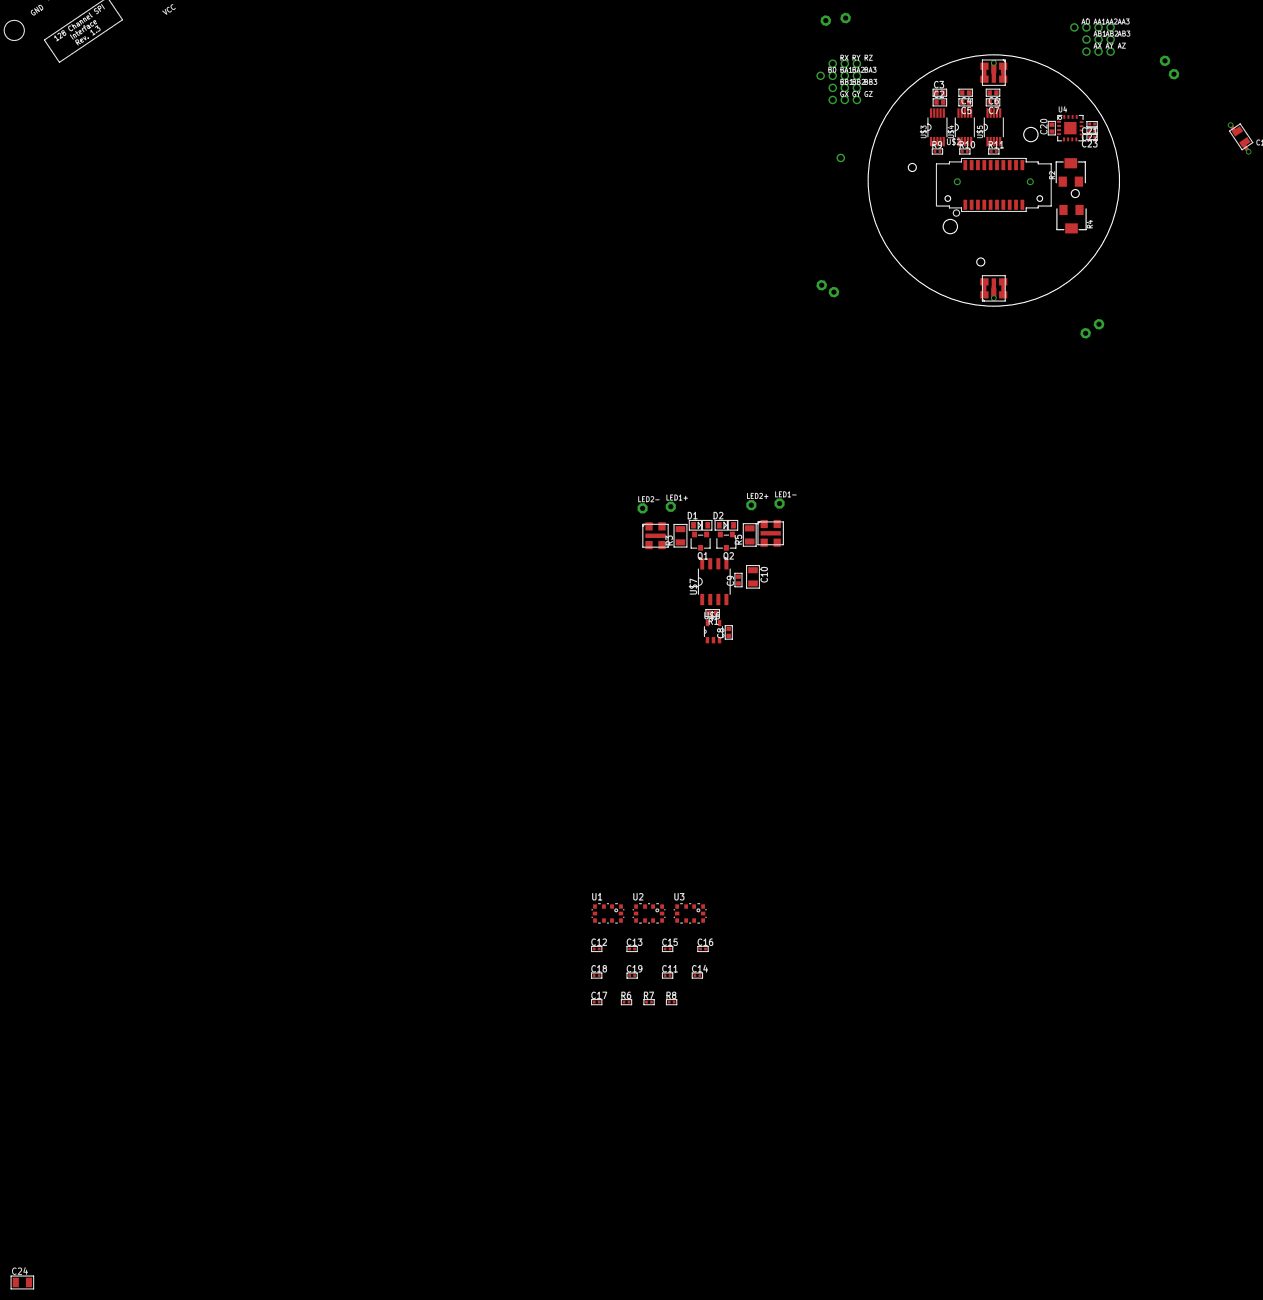
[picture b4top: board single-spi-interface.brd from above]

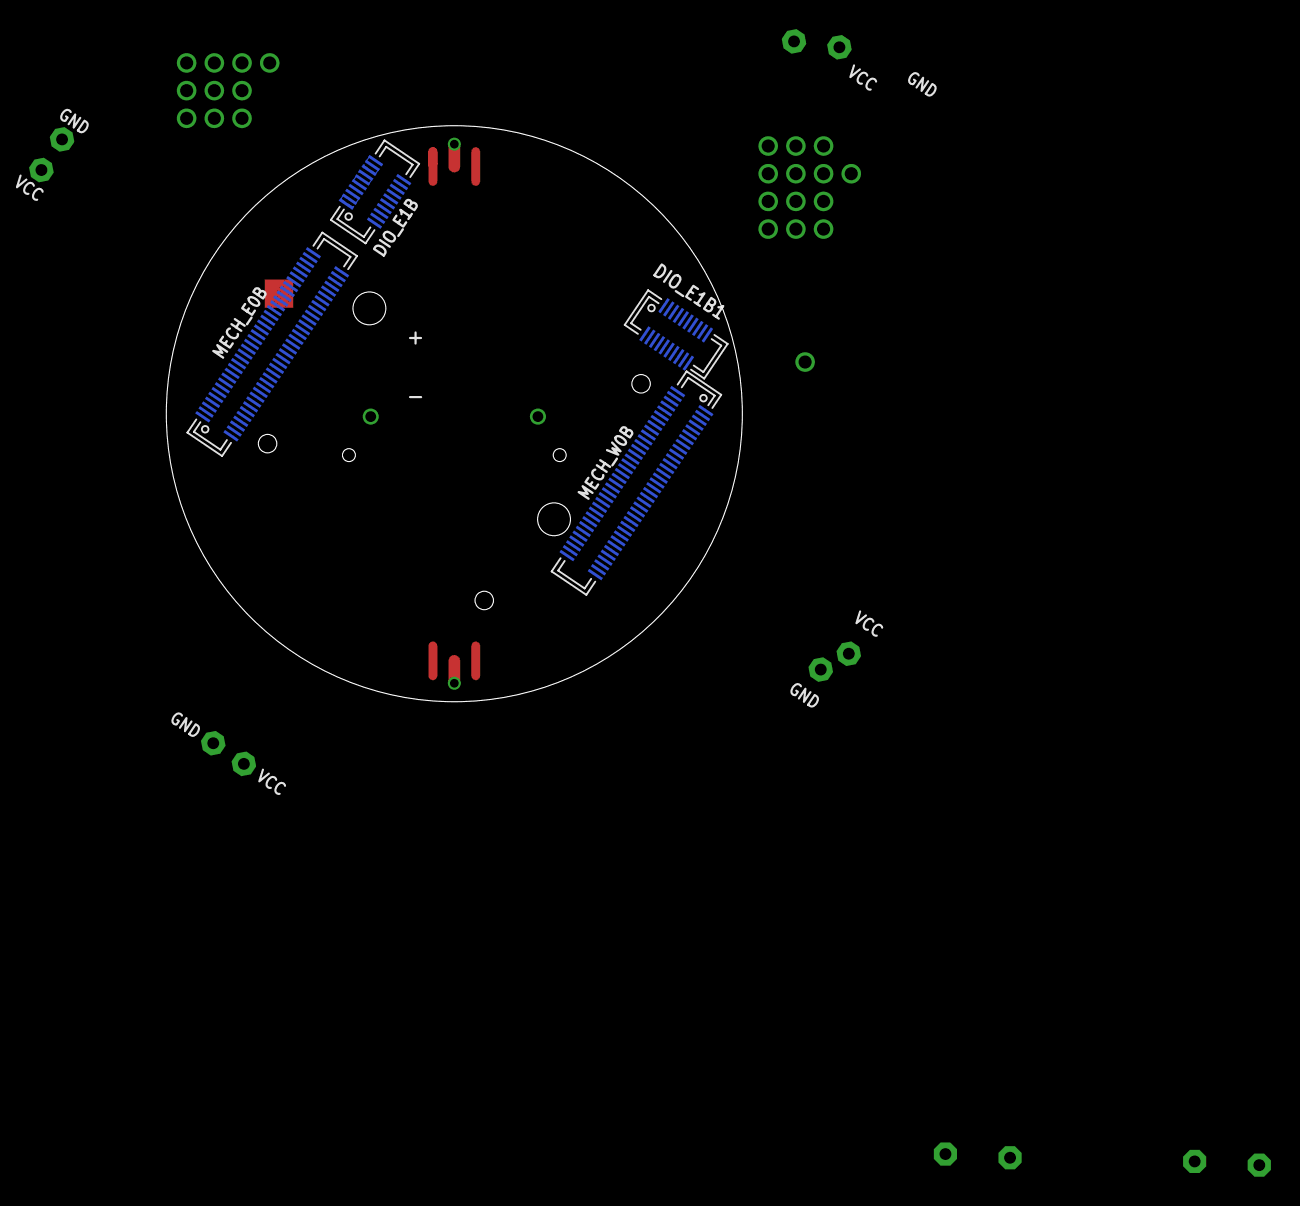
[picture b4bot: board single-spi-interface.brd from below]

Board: 4 copper layers, 39.6 x 39.6 mm, 92 parts (4 on the bottom side), 71 nets.
